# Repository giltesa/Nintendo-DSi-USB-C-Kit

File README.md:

# Nintendo DSi USB-C

The **Nintendo DSi: USB-C** is a board that allows to replace the original charging connector for a modern and standard **USB-C**.

**If your original connector is too old or damaged** and you need a new one, or **if you would like to charge your Nintendo DSi with a standard USB-C charger**, like the charger of your **Nintendo Switch**, phone, laptop, you can with this board.

This board is compatible with these models:

*   Nintendo DSi
*   Nintendo DSi XL

## Would you like it?

https://shop.giltesa.com/product/nintendo-DSi-usb-c-kit/

## More

- [giltesa.com](https://giltesa.com "giltesa.com")
- [twitter.com](https://twitter.com/giltesa "twitter.com")

## License

This project is licensed under a **Creative Commons** license:
**[Attribution-NonCommercial-ShareAlike 4.0 International (CC BY-NC-SA 4.0) ](https://creativecommons.org/licenses/by-nc-sa/4.0/)**

Check the [LICENSE.md](LICENSE.md) for more information.

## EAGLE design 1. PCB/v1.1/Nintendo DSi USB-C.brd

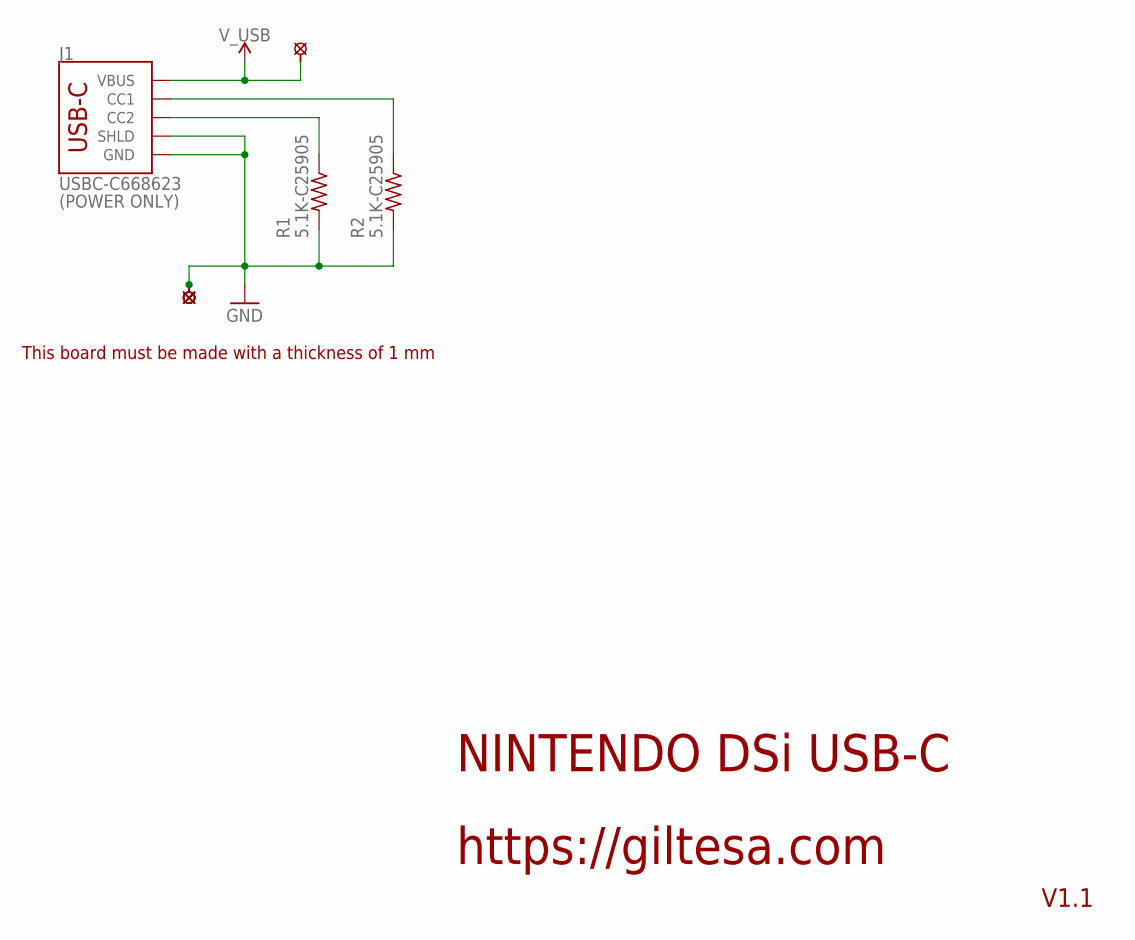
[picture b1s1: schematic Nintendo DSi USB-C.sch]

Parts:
J1: USBC-C668623; USB-C_6P
R1, R2: 5.1K-C25905; R0402
U$2, U$3, U$4, U$5: PAD_1.0H; PAD_1.0_HALF_MASK

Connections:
GND: J1.A12-GND (GND), J1.B12-GND (GND), J1.SHLD1 (SHLD), J1.SHLD2 (SHLD), J1.SHLD3 (SHLD), J1.SHLD4 (SHLD), R1.2, R2.2, U$3.P$1, U$4.P$1, U$5.P$1
unnamed: J1.B5 (CC2), R1.1
unnamed: J1.A5 (CC1), R2.1
V_USB: J1.A9-VBUS (VBUS), J1.B9-VBUS (VBUS), U$2.P$1

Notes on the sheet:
NINTENDO DSi USB-C
https://giltesa.com
V1.1
This board must be made with a thickness of 1 mm
(POWER ONLY)

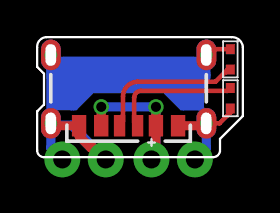
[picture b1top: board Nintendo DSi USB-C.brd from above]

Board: 2 copper layers, 11.0 x 6.2 mm, 8 parts (1 on the bottom side), 4 nets.

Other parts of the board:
U$11: GILTESA.COM_MASK_7MM

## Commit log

2023-08-02 no message
2023-08-20 Added installation guide.
2024-01-15 v1.0
2024-01-15 v1.1

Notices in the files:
parts and their libraries:
SparkFun: Licensing: CC v3.0 Share-Alike You are welcome to use this library for commercial purposes.
SparkFun-PowerSymbols: Licensing: Creative Commons ShareAlike 4.0 International - https://creativecommons.org/licenses/by-sa/4.0
